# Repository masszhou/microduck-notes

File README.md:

# microduck-notes

本仓库保存 Microduck 项目的开发成果、应用、文档和硬件资料。所有本项目的开发和文档修改都在本目录内完成。

## 目录

| 路径 | 内容 |
|---|---|
| [apps/dsh-servo-dashboard](<apps/dsh-servo-dashboard/README.md>) | DSH 多舵机 dashboard、native worker、测试与验证记录 |
| [apps/mac-servo-bench](<apps/mac-servo-bench/README.md>) | OpenRB-150 / XL330 的 Rust 桌面测试工具 |
| [docs](<docs/>) | 物料与研究文档 |
| [hardware/imu_to_dxl](<hardware/imu_to_dxl/README.md>) | IMU 转 DYNAMIXEL 资料和 KiCad 迁移工程 |
| [hardware/Robot_HAT_C1](<hardware/Robot_HAT_C1/README.md>) | 官方 HAT C1 参考工程，保留其 Apache-2.0 许可证 |
| `data/` | 预留的数据目录；当前为空，不由 Git 保存空目录 |

父目录中的 `Fanduck`、`microduck`、`microduck_rl`、`MicroDuck-BoBoRedesign`、`microduck-replica` 是独立的第三方参考目录。本仓库不包含这些目录，不在其中开发，也不将它们加入本仓库的提交。

## 本地验证

以下命令从本仓库根目录运行，不发送真实舵机运动命令：

```sh
npm --prefix apps/dsh-servo-dashboard test
npm --prefix apps/dsh-servo-dashboard run check
cargo test --locked --manifest-path apps/dsh-servo-dashboard/native/Cargo.toml
cargo test --locked --manifest-path apps/mac-servo-bench/Cargo.toml
```

首次 clone 后，在安装 DSH 插件之前构建本机 native worker：

```sh
cargo fetch --locked --manifest-path apps/dsh-servo-dashboard/native/Cargo.toml
npm --prefix apps/dsh-servo-dashboard run build:native
```

再通过 DSH 插件管理器安装当前 clone 中 `apps/dsh-servo-dashboard` 的实际绝对路径。目录移动后需要重新安装本地链接。仓库不保存某一台主机的 DSH profile 配置。

## 版本控制与安全

- 提交源码、Cargo.lock、文档、硬件工程和已有制造/检查资料。
- 忽略 build cache、native 可执行文件、安装包、串口日志、本地 agent checkpoint、凭据和 KiCad 临时状态。已有本地文件不删除。
- `mac-servo-bench` 的 `run`、`home`、`off` 会写真实设备，不能用来验证目录迁移。
- 旋钮实时控制的开发仍暂停。目录迁移和 Git 操作不构成舵机运动授权。
- 本仓库原创内容使用 [MIT License](<LICENSE>)。第三方资料不适用统一的 MIT 重授权，来源与原许可证见 [NOTICE.md](<NOTICE.md>)。

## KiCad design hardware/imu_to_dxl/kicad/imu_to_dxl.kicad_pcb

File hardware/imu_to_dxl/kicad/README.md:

# imu_to_dxl · KiCad K1

2026-09-13。基于本仓库第三方复刻设计，重建为 **KiCad 10 原生、可编辑工程**。已在本机 KiCad 10.0.6 PCB Editor 中实际打开。包含原理图、已布线 PCB、本地符号和封装库。

**这是待打样的复刻原型。** 检查通过说明 KiCad 中的连接与设计规则一致，不能替代器件选型评审、固件开发或实物验证，也不代表恢复了 Pollen Robotics 的官方设计。

## 打开工程

在 KiCad 中打开 [`imu_to_dxl.kicad_pro`](imu_to_dxl.kicad_pro)，随后进入原理图或 PCB 编辑器。移动工程时请复制整个 `kicad` 文件夹；本地库通过 `${KIPRJMOD}` 相对引用，无需安装额外符号库。

| 文件 | 内容 |
|---|---|
| [`imu_to_dxl.kicad_sch`](imu_to_dxl.kicad_sch) | 完整电路、连接器引脚、供电、时钟及总线缓冲 |
| [`imu_to_dxl.kicad_pcb`](imu_to_dxl.kicad_pcb) | 双层布局、走线、过孔、已填充的底层地铜 |
| `imu_to_dxl.kicad_sym`、`sym-lib-table` | 项目符号库与注册表 |
| `imu_to_dxl.pretty/`、`fp-lib-table` | 项目封装库与注册表 |
| [`BOM.md`](BOM.md) | 从源工程元件字段整理的物料表，未查询库存或替代料 |
| [`previews/imu_to_dxl.svg`](previews/imu_to_dxl.svg) | 可放大的原理图预览；同目录另有 PNG |
| [`previews/pcb-top.svg`](previews/pcb-top.svg)、[`previews/pcb-bottom.svg`](previews/pcb-bottom.svg) | 顶层布线与装配轮廓、镜像底层铜；另有 PNG |
| `checks/` | ERC、DRC、引脚核对、网表及移除过孔记录 |
| `source/` | 原始 EDA 文件副本、恢复的设计快照、预期引脚网络表 |

## 板子参数

| 项目 | K1 数值 |
|---|---|
| 外形 | 名义 45 × 22 mm，四角 R2 |
| 层数 / 板厚 | 2 层 / 1.6 mm |
| 安装孔 | 2 个直径 2.2 mm 非金属化孔 |
| 孔中心 | 从板框左下角起，MH1=(2.667, 2.413) mm；MH2=(42.672, 19.685) mm |
| 电子元件 | 29 个；另有 2 个安装孔封装 |
| 电气引脚 | 105 个；23 个有效网络，另有 4 个明确未连接引脚 |
| 走线 / 过孔 | 227 段 / 20 个 |
| 地铜 | B.Cu；已重新填充 |
| 主要设计规则 | 间距 ≥0.15 mm；线宽 ≥0.15 mm；铜到板边 ≥0.30 mm；过孔直径/孔径 ≥0.60/0.30 mm |

板框按资料中的名义尺寸重建，并保留源工程孔位和元件位置。没有将源资料中的“1 oz 铜厚”转为经板厂确认的叠层；生产参数需在打样前确定。

## 接口与源资料差异

以下针脚按**封装焊盘编号**列出；不能仅凭插头朝向或线色推断编号。

| 接口 | 1 | 2 | 3 | 4 | 5 | 6 |
|---|---|---|---|---|---|---|
| J1、J2，EH 2.5 mm | GND | VDD_BUS | DXL_BUS | — | — | — |
| J4、J5，PH 2.0 mm | DXL_BUS | VDD_BUS | GND | — | — | — |
| J3，SWD + UART | GND | SWDCLK | SWDIO | **UART_RX** | **UART_TX** | +3V3 |

J3 的 RX/TX 以板上 MCU 为参照：外部串口 TX 接 J3.4，外部 RX 接 J3.5。源工程实际连接及原理图图片都是 **4=RX、5=TX**，部分文字接线说明则相反；本次按实际工程连接保留。J3 的串口网络属于 3.3 V MCU 引脚。

J4/J5 保留了源工程的 PH 型封装；**尚未确认它与实际飞特线束或 AMP 2.0 插头机械兼容**。两个接口组的第 1、3 脚顺序相反。

源资料的新旧段落另有两处差异，本次按最新 EDA 连接处理：

- `RX_EN` 接 U1.1、U3.7，由 R7 的 10 kΩ 上拉保持默认使能；并非永久直连 3.3 V。`DE` 接 U1.8、U3.1，发送使能为低有效。
- X1 为 16 MHz **有源振荡器**，X1、C9、R3 均设置为装配。输出经 R3=33 Ω 接 U1.2 `PC14 / OSC_IN`，不是早期文档所述默认 DNP 的无源晶体。固件仍需正确配置时钟。

## 重建方法与改动

源文件是嘉立创 EDA 专业版 `.eprj2`。从其保存历史恢复了最新原理图、PCB、器件和库对象，再写成原生 KiCad 对象；没有把原理图或 PCB 图片当作不可编辑底图。

保留了源工程的器件、引脚网络、焊盘几何、布局与 227 段走线；U4 的不规则铜焊盘作为 KiCad 自定义焊盘保留。处理删除过的原理图线段时，同时核对了其所属 WIRE 对象，避免把历史孤立线段恢复为错误连接。

K1 的明确改动如下：

1. 按名义 45 × 22 mm、R2 重建原生板框；安装孔沿用源坐标。
2. 将 `3.3V` 命名为 `+3V3`，振荡器输出自动网名改为 `Net-(X1-OUTPUT)`；KiCad 局部标签生成的 `/` 前缀只影响名称显示。
3. 添加电气引脚类型、未连接标记和供电标记；关联原理图与 PCB，保留器件型号、立创编号和数据手册字段。
4. 整理原理图标注及 PCB 位号、首脚／阴极标记。原封装的外形图移到 F.Fab，减少丝印与焊盘冲突。
5. 移除 **11 个仅在底层连接地铜、顶层没有连接的多余 GND 过孔**，对应 KiCad 的 `via_dangling` 报告。未移除信号或电源走线；坐标见 [`checks/removed_unused_vias.json`](checks/removed_unused_vias.json)。
6. 原文件的独立泪滴铜形状未导入；K1 使用走线、焊盘和地铜本身连接。封装未添加完整 courtyard 装配间隙轮廓或 3D 模型。

## 已完成的数字检查

| 检查 | 结果 | 证据 |
|---|---|---|
| 源工程逐引脚与 KiCad 原理图网表比对 | 29 个元件、105 个电气引脚，0 不一致 | [`pin_net_comparison.json`](checks/pin_net_comparison.json) |
| KiCad ERC | 0 项错误或警告 | [`erc.json`](checks/erc.json) |
| KiCad PCB DRC | 0 项错误或警告 | [`drc.json`](checks/drc.json) |
| 未连接项 | 0 | 同上 |
| 原理图与 PCB 一致性 | 0 项问题 | 同上 |
| 文件与画面 | 原生工程已在 KiCad 打开；原理图及正反面输出已查看 | `previews/` |

没有添加逐项 DRC 排除项。报告保留了 KiCad 默认忽略的检查项，其中包括 `missing_courtyard`；由于没有完整装配间隙轮廓，**上述结果不覆盖器件本体、插头外壳与机械结构碰撞**。也没有独立完成全部器件数据手册及保护电路的工程复审。

迁移检查补充（2026-11-07）：历史 `checks/artifact_sha256.json` 的 38 项中有 37 项与当前文件一致。`imu_to_dxl.kicad_pro` 当前 hash 为 `4b3cdba5b32d82fef5dfe11ee7cdbdc6113b2f1c7b8b1176bce5723d7bc6e814`，与历史记录不同；文件修改时间为 2026-09-20，早于本次迁移检查。本次保留当前配置，不重写历史清单，也不据历史 ERC/DRC 报告宣称当前配置已经重新验证。

## 尚需验证

- **固件**：本次没有编写或烧录固件。让它在总线上表现为舵机、响应目标 ID 与寄存器读取，需要 MCU 的协议、半双工方向控制、IMU 读取与时钟配置。1 Mbps 通信、姿态轴向和数据格式尚未实测。
- **连接与装配**：核实购买的连接器系列、首脚朝向、线束顺序、实际封装尺寸、安装孔和整机空间。无 3D 模型的 PCB 视图不能证明装配适配。
- **通电与负载**：尚未打样、焊接、通电或测量波形。源布局的总线电源路径及接插件没有做下游舵机电流／温升验证；F1 保护本板供电分支，并不限制总线直通支路的电流。

## 复现与维护

正常修改请直接使用 KiCad；下面的脚本仅用于复现迁移。**重新运行生成脚本会覆盖原生工程，不适合在手工修改之后直接运行。**

迁入 `microduck-notes` 后，`checks/netlist.xml` 中的 `design/source` 已规范化为相对报告文件的路径，不再保存开发者的 home 路径。其余网表与日期保留历史结果；这不是一次新的 ERC/DRC 验证。重新导出报告时，提交前需要再次检查本机路径。

需要带 `pcbnew` 的 KiCad Python。当前 Mac 的解释器位于 `/Applications/KiCad/KiCad.app/Contents/Frameworks/Python.framework/Versions/3.9/bin/python3.9`。

1. `build_kicad.py`：从 `source/design.json` 生成初始工程，此时包含源文件的 31 个过孔。
2. `finish_silkscreen.py`：整理 F.Fab、丝印位号和首脚标记。
3. `sync_and_verify.py`：导出原理图网表，核对全部引脚，同步 PCB 网络／元件字段和本地封装库。
4. 运行 `kicad-cli pcb drc --refill-zones --save-board --schematic-parity --format json -o checks/initial-drc.json imu_to_dxl.kicad_pcb`。
5. 仅针对这份新报告运行 `remove_unused_vias.py checks/initial-drc.json`；不能复用旧板的报告。
6. 再次填铜并运行 DRC／原理图一致性检查，同时运行 `kicad-cli sch erc --format json -o checks/erc.json imu_to_dxl.kicad_sch`。交付的 `checks/drc.json` 是最终报告。

源快照只包含绘图和库对象，不包含运行本次转换所需的外部服务依赖。原 `.eprj2` 副本同时保留，方便回到原软件核查。

## 来源与署名

第三方设计来源：[fanhao375/microduck-replica](https://github.com/fanhao375/microduck-replica)，本地基线提交 `c2d2ffefc133437add912961917fe5049a287a7b`，路径 `hardware/imu_to_dxl/`。本次使用同目录的 EDA 工程、原理图／PCB 图纸及逆向说明。

源 `.eprj2` 的 SHA-256：`4fef83c09d2db93c257a41728f3a30559384a1a201ccc825cb206e3c4bb9a243`。

EDA 文件读取方法参考 [Dao-PCB-Design-Agent 的格式解码实现](https://github.com/dao-genesis/Dao-PCB-Design-Agent/blob/main/lceda_bridge/cdp_studio/eprj2_codec.py)；对象几何解释参考 [KiCad 官方 EasyEDA Pro 导入器](https://gitlab.com/kicad/code/kicad/-/tree/master/pcbnew/pcb_io/easyedapro)。本目录的转换脚本为本次编写。

原资料的署名和许可证约定见仓库 [`NOTICE.md`](../../../NOTICE.md) 与 [`LICENSE`](../../../LICENSE)。本次迁移保留来源，不为第三方设计另行指定许可。K1 与 Pollen Robotics 无隶属或背书关系。

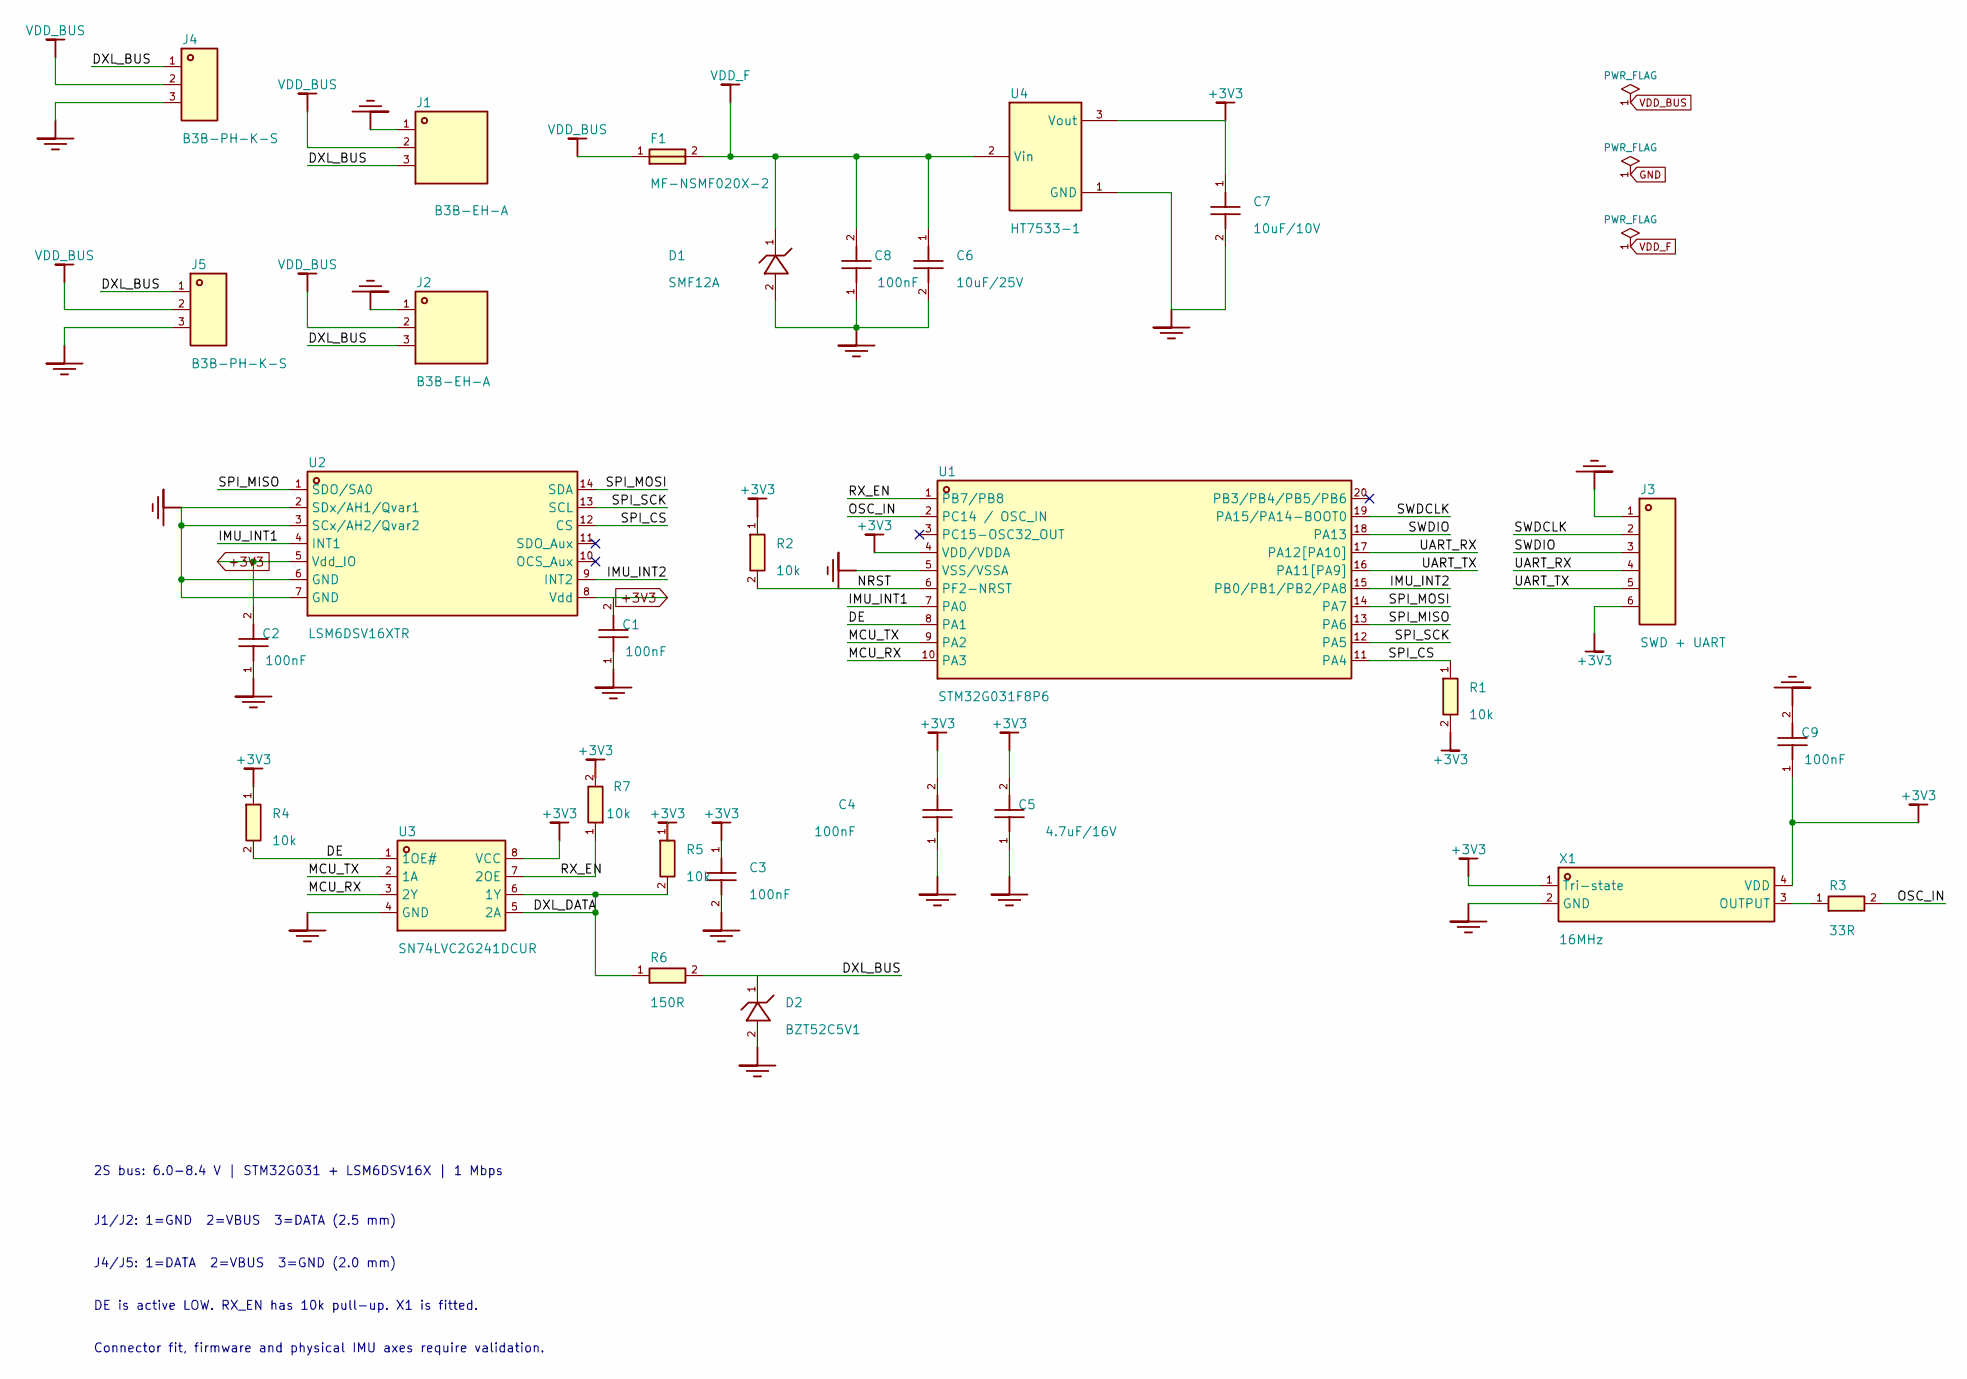
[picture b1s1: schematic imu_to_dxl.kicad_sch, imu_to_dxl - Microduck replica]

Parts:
C1: 100nF; C1_C0603; Manufacturer Part CC0603KRX7R9BB104; LCSC C14663
C2: 100nF; C2_C0603; Manufacturer Part CC0603KRX7R9BB104; LCSC C14663
C3: 100nF; C3_C0603; Manufacturer Part CC0603KRX7R9BB104; LCSC C14663
C4: 100nF; C4_C0603; Manufacturer Part CC0603KRX7R9BB104; LCSC C14663
C5: 4.7uF/16V; C5_C0603; Manufacturer Part CL10A475KO8NNNC; LCSC C19666
C6: 10uF/25V; C6_C0805; Manufacturer Part CL21A106KAYNNNE; LCSC C15850
C7: 10uF/10V; C7_C0603; Manufacturer Part CL10A106KP8NNNC; LCSC C19702
C8: 100nF; C8_C0603; Manufacturer Part CC0603KRX7R9BB104; LCSC C14663
C9: 100nF; C9_C0603; Manufacturer Part CC0603KRX7R9BB104; LCSC C14663
D1: SMF12A; D1_SOD-123FL_L2_7-W1_8-LS3_7-RD; Manufacturer Part SMF12A; LCSC C2943870
D2: BZT52C5V1; D2_SOD-123_L2_7-W1_6-LS3_7-RD; Manufacturer Part BZT52C5V1-7-F; LCSC C151588
F1: MF-NSMF020X-2; F1_F1206; Manufacturer Part MF-NSMF020X-2; LCSC C210358
J1: B3B-EH-A; J1_CONN-TH_B3B-EH-A-LF-SN; Manufacturer Part B3B-EH-A(LF)(SN); LCSC C160259
J2: B3B-EH-A; J2_CONN-TH_B3B-EH-A-LF-SN; Manufacturer Part B3B-EH-A(LF)(SN); LCSC C160259
J3: SWD + UART; J3_HDR-TH_6P-P2_54-V-M; Manufacturer Part PZ254V-11-06P; LCSC C492405
J4: B3B-PH-K-S; J4_CONN-TH_B3B-PH-K-S; Manufacturer Part B3B-PH-K-S(LF)(SN); LCSC C131339
J5: B3B-PH-K-S; J5_CONN-TH_B3B-PH-K-S; Manufacturer Part B3B-PH-K-S(LF)(SN); LCSC C131339
R1: 10k; R1_R0603; Manufacturer Part 0603WAF1002T5E; LCSC C25804
R2: 10k; R2_R0603; Manufacturer Part 0603WAF1002T5E; LCSC C25804
R3: 33R; R3_R0603; Manufacturer Part 0603WAF330JT5E; LCSC C23140
R4: 10k; R4_R0603; Manufacturer Part 0603WAF1002T5E; LCSC C25804
R5: 10k; R5_R0603; Manufacturer Part 0603WAF1002T5E; LCSC C25804
R6: 150R; R6_R0603; Manufacturer Part 0603WAF1500T5E; LCSC C22808
R7: 10k; R7_R0603; Manufacturer Part 0603WAF1002T5E; LCSC C25804
U1: STM32G031F8P6; U1_TSSOP-20_L6_5-W4_4-P0_65-LS6_4-BL; Manufacturer Part STM32G031F8P6; LCSC C529334
U2: LSM6DSV16XTR; U2_LGA-14_L3_0-W2_5-P0_50-BR; Manufacturer Part LSM6DSV16XTR; LCSC C5267406
U3: SN74LVC2G241DCUR; U3_VSSOP-8_L2_3-W2_0-P0_50-LS3_1-BR; Manufacturer Part SN74LVC2G241DCUR; LCSC C10430
U4: HT7533-1; U4_SOT-89-3_L4_5-W2_5-P1_50-LS4_2-BR; Manufacturer Part HT7533-1; LCSC C14289
X1: 16MHz; X1_OSC-SMD_4P-L3_2-W2_5-BL_SIT8008BI; Manufacturer Part S3D16.000000B20F30T; LCSC C387369

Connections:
+3V3: C1.2, C2.2, C3.1, C4.2, C5.2, C7.1, C9.1, J3.6, R1.2, R2.1, R4.1, R5.1, R7.2, U1.4 (VDD/VDDA), U2.5 (Vdd_IO), U2.8 (Vdd), U3.8 (VCC), U4.3 (Vout), X1.1 (Tri-state), X1.4 (VDD)
/DE: R4.2, U1.8 (PA1), U3.1 (1OE#)
/DXL_BUS: D2.1, J1.3, J2.3, J4.1, J5.1, R6.2
/DXL_DATA: R5.2, R6.1, U3.5 (2A), U3.6 (1Y)
/IMU_INT1: U1.7 (PA0), U2.4 (INT1)
/IMU_INT2: U1.15 (PB0/PB1/PB2/PA8), U2.9 (INT2)
/MCU_RX: U1.10 (PA3), U3.3 (2Y)
/MCU_TX: U1.9 (PA2), U3.2 (1A)
/NRST: R2.2, U1.6 (PF2-NRST)
/OSC_IN: R3.2, U1.2 (PC14 / OSC_IN)
/RX_EN: R7.1, U1.1 (PB7/PB8), U3.7 (2OE)
/SPI_CS: R1.1, U1.11 (PA4), U2.12 (CS)
/SPI_MISO: U1.13 (PA6), U2.1 (SDO/SA0)
/SPI_MOSI: U1.14 (PA7), U2.14 (SDA)
/SPI_SCK: U1.12 (PA5), U2.13 (SCL)
/SWDCLK: J3.2, U1.19 (PA15/PA14-BOOT0)
/SWDIO: J3.3, U1.18 (PA13)
/UART_RX: J3.4, U1.17 (PA12[PA10])
/UART_TX: J3.5, U1.16 (PA11[PA9])
GND: C1.1, C2.1, C3.2, C4.1, C5.1, C6.2, C7.2, C8.1, C9.2, D1.2, D2.2, J1.1, J2.1, J3.1, J4.3, J5.3, U1.5 (VSS/VSSA), U2.2 (SDx/AH1/Qvar1), U2.3 (SCx/AH2/Qvar2), U2.6 (GND), U2.7 (GND), U3.4 (GND), U4.1 (GND), X1.2 (GND)
unnamed: R3.1, X1.3 (OUTPUT)
VDD_BUS: F1.1, J1.2, J2.2, J4.2, J5.2
VDD_F: C6.1, C8.2, D1.1, F1.2, U4.2 (Vin)

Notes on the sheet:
2S bus: 6.0-8.4 V | STM32G031 + LSM6DSV16X | 1 Mbps
J1/J2: 1=GND 2=VBUS 3=DATA (2.5 mm)
J4/J5: 1=DATA 2=VBUS 3=GND (2.0 mm)
DE is active LOW. RX_EN has 10k pull-up. X1 is fitted.
Connector fit, firmware and physical IMU axes require validation.

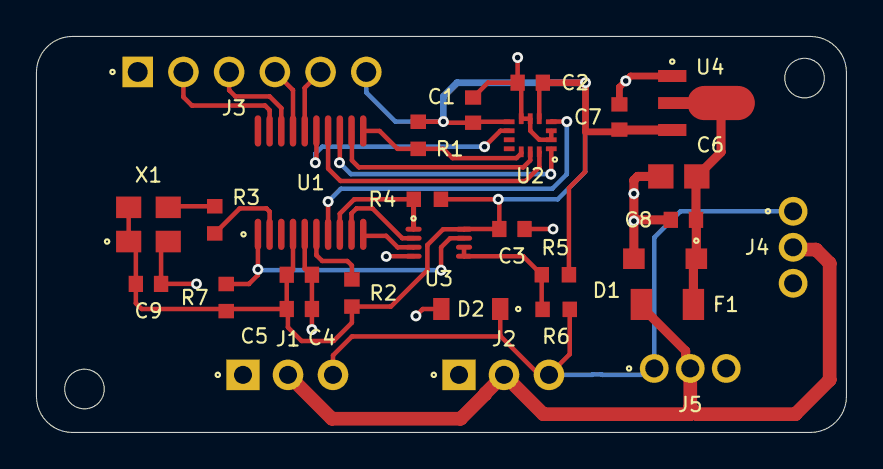
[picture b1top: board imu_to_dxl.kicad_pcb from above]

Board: 2 copper layers, 45.0 x 22.0 mm, 31 parts (0 on the bottom side), 23 nets.

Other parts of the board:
MH1, MH2: (no value)
